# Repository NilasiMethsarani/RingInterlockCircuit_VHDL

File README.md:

Ring Interlock Circuit for EV Charging

This repository contains the design and implementation of a Ring Interlock Circuit for electric vehicle (EV) charging, using a CPLD (Complex Programmable Logic Device), specifically the EPM240T100C5N. The interlock circuit enhances the safety, efficiency, and reliability of EV charging systems by ensuring dynamic power sharing and robust fault prevention mechanisms.
Key Features

    Dynamic Power Sharing: Efficient distribution of power between multiple EVs to optimize charging performance.
    Enhanced Prioritization: Ensures prioritized power delivery based on load requirements.
    Short Circuit Prevention: Detects and prevents potential short circuits during charging.
    Compact and Scalable Design: Designed for scalability, leveraging the EPM240T100C5N CPLD for cost-effective implementation.

Design Components

    Technology Used:
        CPLD Model: EPM240T100C5N
        Quartus Prime for synthesis and implementation.
        ModelSim for simulation.
        Proteus for circuit-level design and testing.

    Input Signals:
        EV charging status.
        Fault detection inputs.
        Load conditions for power prioritization.

    Output Signals:
        Control signals to charging ports.
        Fault notifications.
        Power allocation indicators.

Objectives

    Ensure safe and efficient charging of multiple EVs using an interlock mechanism.
    Provide a cost-effective solution with minimal hardware overhead.
    Test and validate the design against real-world fault conditions.

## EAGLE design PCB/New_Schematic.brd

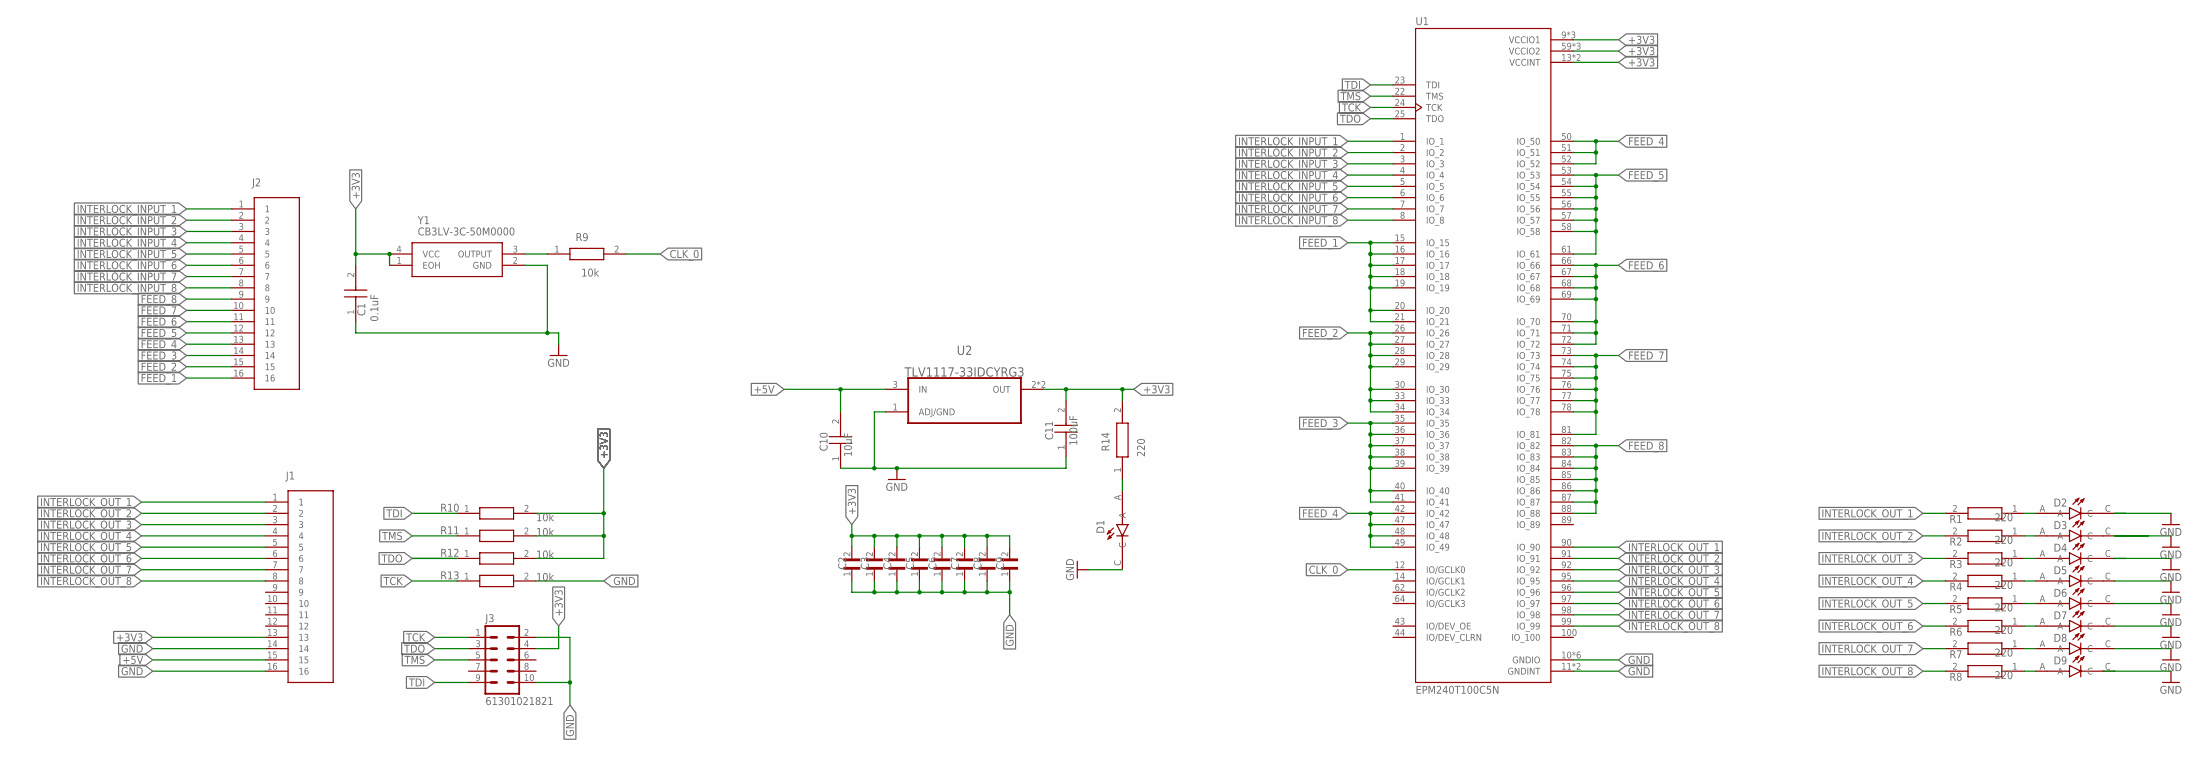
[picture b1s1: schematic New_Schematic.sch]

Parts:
C1: GRM188R71C104MA01D; CAPC1608X90N
C2, C3, C4, C5, C6, C7, C8, C9: GRM155R70J104KA01D; CAPC1005X55N
C10, C11: 0603X106M160CT; CAPC1608X95N
D1, D2, D3, D4, D5, D6, D7, D8, D9: HSMS-C190; LEDM1608X80
J1, J2: 1-2314812-6; TE_1-2314812-6
J3: 61301021821; 2X05-PIN
R1, R2, R3, R4, R5, R6, R7, R8, R14: MCT06030D2200BP100; RESC1608X55N
R9, R10, R11, R12, R13: CRT0603-BY-1002EAS; RESC1608X60N
U1: EPM240T100C5N; QFP50P1600X1600X120-100N
U2: TLV1117-33IDCYRG3; SOT230P700X180-4N
Y1: CB3LV-3C-50M0000; CB3LV3C50M0000

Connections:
+3V3: C1.2, C2.2, C3.2, C4.2, C5.2, C6.2, C7.2, C8.2, C9.2, C11.2, J1.13, J3.4, R10.2, R11.2, R12.2, R14.2, U1.9 (VCCIO1), U1.13 (VCCINT), U1.31 (VCCIO1), U1.45 (VCCIO1), U1.59 (VCCIO2), U1.63 (VCCINT), U1.80 (VCCIO2), U1.94 (VCCIO2), U2.2 (OUT), U2.4 (OUT), Y1.1 (EOH), Y1.4 (VCC)
+5V: C10.2, J1.15, U2.3 (IN)
CLK_0: R9.2, U1.12 (IO/GCLK0)
FEED_1: J2.16, U1.15 (IO_15), U1.16 (IO_16), U1.17 (IO_17), U1.18 (IO_18), U1.19 (IO_19), U1.20 (IO_20), U1.21 (IO_21)
FEED_2: J2.15, U1.26 (IO_26), U1.27 (IO_27), U1.28 (IO_28), U1.29 (IO_29), U1.30 (IO_30), U1.33 (IO_33), U1.34 (IO_34)
FEED_3: J2.14, U1.35 (IO_35), U1.36 (IO_36), U1.37 (IO_37), U1.38 (IO_38), U1.39 (IO_39), U1.40 (IO_40), U1.41 (IO_41)
FEED_4: J2.13, U1.42 (IO_42), U1.47 (IO_47), U1.48 (IO_48), U1.49 (IO_49), U1.50 (IO_50), U1.51 (IO_51), U1.52 (IO_52)
FEED_5: J2.12, U1.53 (IO_53), U1.54 (IO_54), U1.55 (IO_55), U1.56 (IO_56), U1.57 (IO_57), U1.58 (IO_58), U1.61 (IO_61)
FEED_6: J2.11, U1.66 (IO_66), U1.67 (IO_67), U1.68 (IO_68), U1.69 (IO_69), U1.70 (IO_70), U1.71 (IO_71), U1.72 (IO_72)
FEED_7: J2.10, U1.73 (IO_73), U1.74 (IO_74), U1.75 (IO_75), U1.76 (IO_76), U1.77 (IO_77), U1.78 (IO_78), U1.81 (IO_81)
FEED_8: J2.9, U1.82 (IO_82), U1.83 (IO_83), U1.84 (IO_84), U1.85 (IO_85), U1.86 (IO_86), U1.87 (IO_87), U1.88 (IO_88)
GND: C1.1, C2.1, C3.1, C4.1, C5.1, C6.1, C7.1, C8.1, C9.1, C10.1, C11.1, D1.C, D2.C, D3.C, D4.C, D5.C, D6.C, D7.C, D8.C, D9.C, J1.14, J1.16, J3.2, J3.10, R13.2, U1.10 (GNDIO), U1.11 (GNDINT), U1.32 (GNDIO), U1.46 (GNDIO), U1.60 (GNDIO), U1.65 (GNDINT), U1.79 (GNDIO), U1.93 (GNDIO), U2.1 (ADJ/GND), Y1.2 (GND)
INTERLOCK_INPUT_1: J2.1, U1.1 (IO_1)
INTERLOCK_INPUT_2: J2.2, U1.2 (IO_2)
INTERLOCK_INPUT_3: J2.3, U1.3 (IO_3)
INTERLOCK_INPUT_4: J2.4, U1.4 (IO_4)
INTERLOCK_INPUT_5: J2.5, U1.5 (IO_5)
INTERLOCK_INPUT_6: J2.6, U1.6 (IO_6)
INTERLOCK_INPUT_7: J2.7, U1.7 (IO_7)
INTERLOCK_INPUT_8: J2.8, U1.8 (IO_8)
INTERLOCK_OUT_1: J1.1, R1.2, U1.90 (IO_90)
INTERLOCK_OUT_2: J1.2, R2.2, U1.91 (IO_91)
INTERLOCK_OUT_3: J1.3, R3.2, U1.92 (IO_92)
INTERLOCK_OUT_4: J1.4, R4.2, U1.95 (IO_95)
INTERLOCK_OUT_5: J1.5, R5.2, U1.96 (IO_96)
INTERLOCK_OUT_6: J1.6, R6.2, U1.97 (IO_97)
INTERLOCK_OUT_7: J1.7, R7.2, U1.98 (IO_98)
INTERLOCK_OUT_8: J1.8, R8.2, U1.99 (IO_99)
unnamed: D2.A, R1.1
unnamed: D3.A, R2.1
unnamed: D4.A, R3.1
unnamed: D5.A, R4.1
unnamed: D6.A, R5.1
unnamed: D7.A, R6.1
unnamed: D8.A, R7.1
unnamed: D9.A, R8.1
unnamed: R9.1, Y1.3 (OUTPUT)
unnamed: D1.A, R14.1
TCK: J3.1, R13.1, U1.24 (TCK)
TDI: J3.9, R10.1, U1.23 (TDI)
TDO: J3.3, R12.1, U1.25 (TDO)
TMS: J3.5, R11.1, U1.22 (TMS)

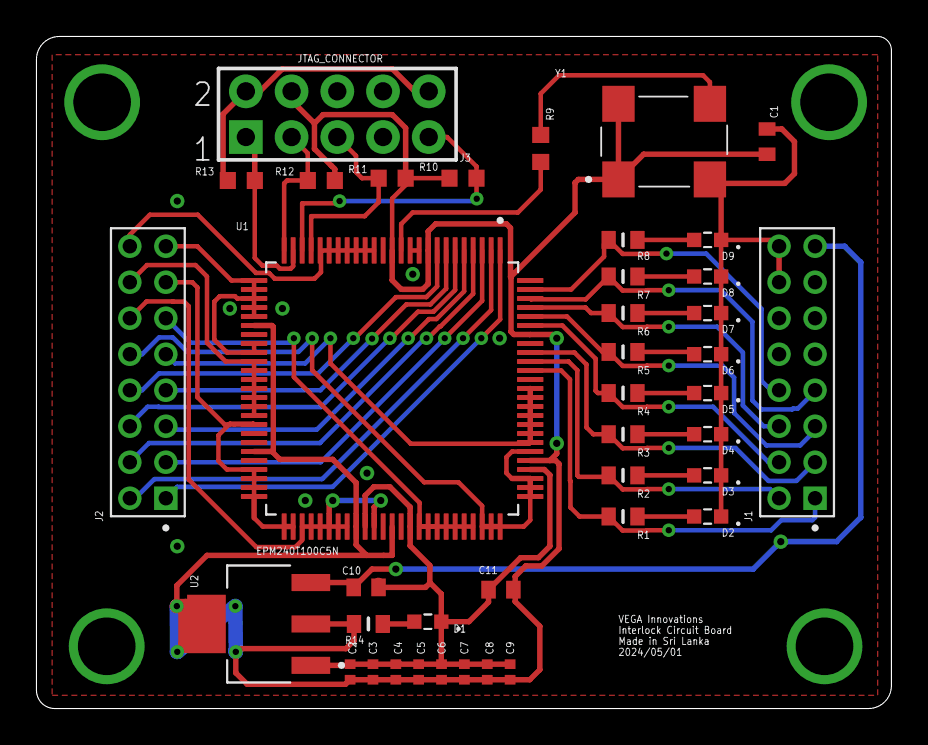
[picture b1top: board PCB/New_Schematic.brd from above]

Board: 2 copper layers, 47.5 x 37.3 mm, 40 parts (0 on the bottom side), 42 nets.

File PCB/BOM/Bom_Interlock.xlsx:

Part | Qty | Manufacturer | Manufacturer Part Number | DigiKey Part Number | LCSC Part Number | Description | Link
J1, J2 | 2 | TE Connectivity AMP Connectors | 1-2314812-6 | 17-1-2314812-6-ND |  | 16P,2MM,B-B,REC,DRVT,2.0,0.1AU,T | Link
J3 | 1 | Würth Elektronik | 61301021821 | 732-2861-ND |  | CONN HDR 10POS 0.1 GOLD PCB | Link
R1, R2, R3, R4, R5, R6, R7, R8, R14 | 9 | Stackpole Electronics Inc | RMCF0603JT220R | RMCF0603JT220RTR-ND |  | RES 220 OHM 5% 1/10W 0603 | Link
R9, R10, R11, R12, R13 | 5 | Bourns Inc. | CRT0603-BY-1002EAS | CRT0603-BY-1002EASTR-ND |  | RES SMD 10K OHM 1/10W 0.1% 0603 | Link
C1, C2, C3, C4, C5, C6, C7, C8, C9 | 9 | Murata Electronics | GRM188R71C104MA01D | 490-11510-2-ND |  | CAP CER 0.1UF 16V X7R 0603 | Link
C10 | 1 | Murata Electronics | GRM188R61C106MAALD | 490-10729-2-ND |  | CAP CER 10UF 16V X5R 0603 | Link
C11 | 1 | KEMET | C0603C104K4RAC3077 | 399-C0603C104K4RAC3077TR-ND |  | .100UF 16.0V | Link
D1, D2, D3, D4, D5, D6, D7, D8, D9 | 9 | Broadcom Limited | HSMS-C190 | 516-1422-2-ND |  | LED RED DIFFUSED SMD | Link
Y1 | 1 | CTS-Frequency Controls | CB3LV-3C-50M000000 | 110-CB3LV-3C-50M000000TR-ND |  | XTAL OSC XO 50.0000MHZ HCMOS TTL | Link
U1 | 1 | Intel | EPM240T100C5N | 544-1964-ND | C10041 | IC CPLD 192MC 4.7NS 100TQFP | Link
U2 | 1 | Texas Instruments | TLV1117-33IDCYRG3 | 296-50543-2-ND |  | IC REG LIN 3.3V 800MA SOT223-4 | Link

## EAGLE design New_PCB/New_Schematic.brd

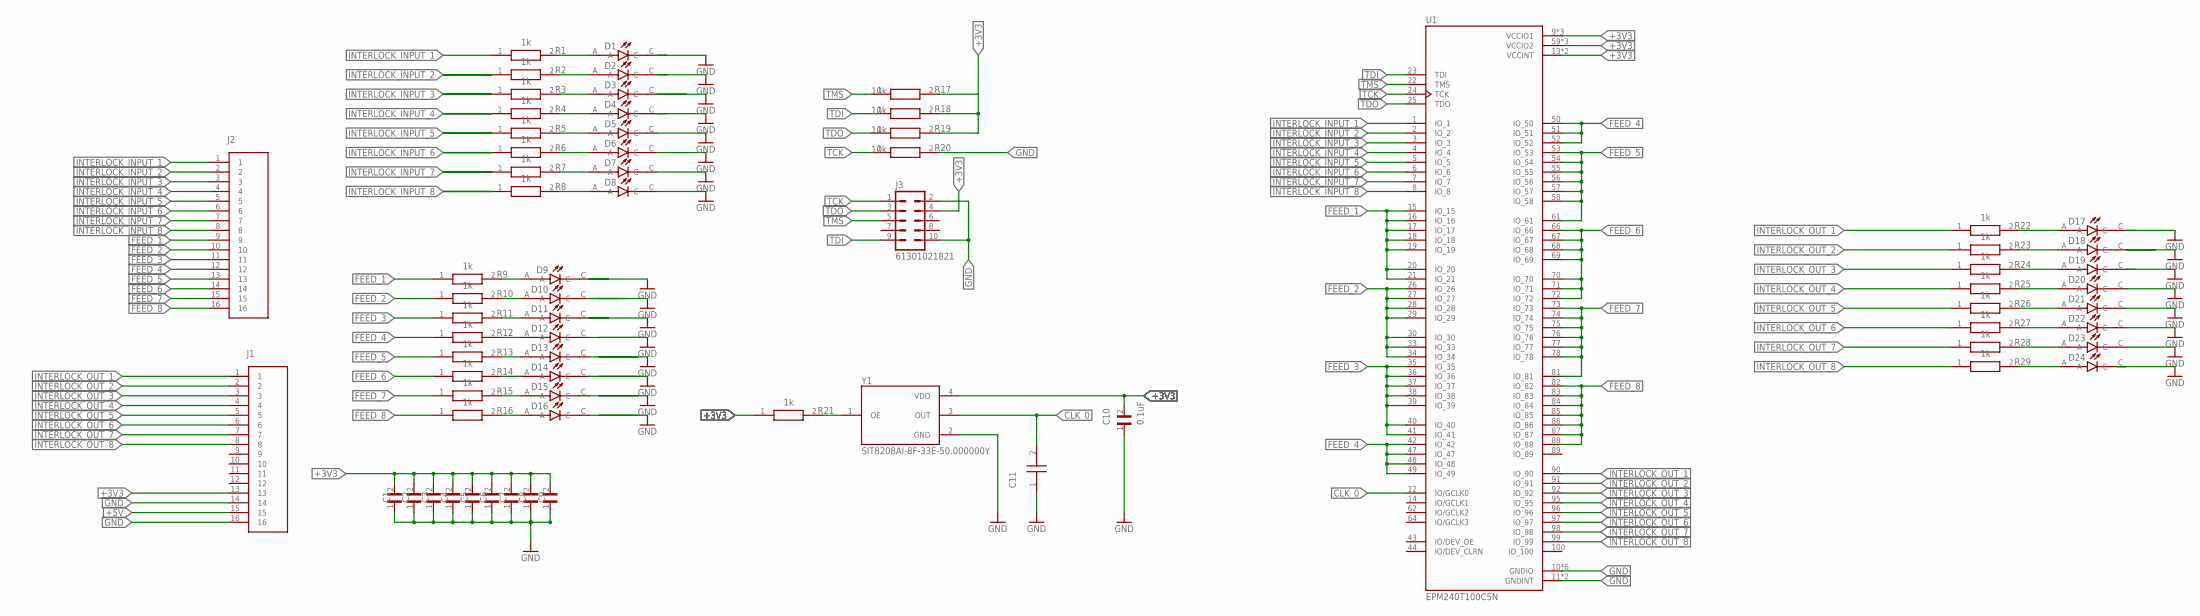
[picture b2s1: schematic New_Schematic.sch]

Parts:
C1, C2, C3, C4, C5, C6, C7, C8, C9, C10: GRM155R70J104KA01D; CAPC1005X55N
C11: GRM1883U2A150JZ01B; CAPC1608X90N
D1, D2, D3, D4, D5, D6, D7, D8, D9, D10, D11, D12, D13, D14, D15, D16, D17, D18, D19, D20, D21, D22, D23, D24: HSMS-C190; LEDM1608X80
J1, J2: 1-2314812-6; TE_1-2314812-6
J3: 61301021821; 2X05-PIN
R1, R2, R3, R4, R5, R6, R7, R8, R9, R10, R11, R12, R13, R14, R15, R16, R21, R22, R23, R24, R25, R26, R27, R28, R29: ERJS03D1001V; RESC1608X55N
R17, R18, R19, R20: CRT0603-BY-1002EAS; RESC1608X60N
U1: EPM240T100C5N; QFP50P1600X1600X120-100N
Y1: SIT8208AI-8F-33E-50.000000Y; OSC_SIT8208AI-8F-33E-50.000000Y

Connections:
+3V3: C1.2, C2.2, C3.2, C4.2, C5.2, C6.2, C7.2, C8.2, C9.2, C10.2, J1.13, J3.4, R17.2, R18.2, R19.2, R21.1, U1.9 (VCCIO1), U1.13 (VCCINT), U1.31 (VCCIO1), U1.45 (VCCIO1), U1.59 (VCCIO2), U1.63 (VCCINT), U1.80 (VCCIO2), U1.94 (VCCIO2), Y1.4 (VDD)
+5V: J1.15
CLK_0: C11.2, U1.12 (IO/GCLK0), Y1.3 (OUT)
FEED_1: J2.9, R9.1, U1.15 (IO_15), U1.16 (IO_16), U1.17 (IO_17), U1.18 (IO_18), U1.19 (IO_19), U1.20 (IO_20), U1.21 (IO_21)
FEED_2: J2.10, R10.1, U1.26 (IO_26), U1.27 (IO_27), U1.28 (IO_28), U1.29 (IO_29), U1.30 (IO_30), U1.33 (IO_33), U1.34 (IO_34)
FEED_3: J2.11, R11.1, U1.35 (IO_35), U1.36 (IO_36), U1.37 (IO_37), U1.38 (IO_38), U1.39 (IO_39), U1.40 (IO_40), U1.41 (IO_41)
FEED_4: J2.12, R12.1, U1.42 (IO_42), U1.47 (IO_47), U1.48 (IO_48), U1.49 (IO_49), U1.50 (IO_50), U1.51 (IO_51), U1.52 (IO_52)
FEED_5: J2.13, R13.1, U1.53 (IO_53), U1.54 (IO_54), U1.55 (IO_55), U1.56 (IO_56), U1.57 (IO_57), U1.58 (IO_58), U1.61 (IO_61)
FEED_6: J2.14, R14.1, U1.66 (IO_66), U1.67 (IO_67), U1.68 (IO_68), U1.69 (IO_69), U1.70 (IO_70), U1.71 (IO_71), U1.72 (IO_72)
FEED_7: J2.15, R15.1, U1.73 (IO_73), U1.74 (IO_74), U1.75 (IO_75), U1.76 (IO_76), U1.77 (IO_77), U1.78 (IO_78), U1.81 (IO_81)
FEED_8: J2.16, R16.1, U1.82 (IO_82), U1.83 (IO_83), U1.84 (IO_84), U1.85 (IO_85), U1.86 (IO_86), U1.87 (IO_87), U1.88 (IO_88)
GND: C1.1, C2.1, C3.1, C4.1, C5.1, C6.1, C7.1, C8.1, C9.1, C10.1, C11.1, D1.C, D2.C, D3.C, D4.C, D5.C, D6.C, D7.C, D8.C, D9.C, D10.C, D11.C, D12.C, D13.C, D14.C, D15.C, D16.C, D17.C, D18.C, D19.C, D20.C, D21.C, D22.C, D23.C, D24.C, J1.14, J1.16, J3.2, J3.10, R20.2, U1.10 (GNDIO), U1.11 (GNDINT), U1.32 (GNDIO), U1.46 (GNDIO), U1.60 (GNDIO), U1.65 (GNDINT), U1.79 (GNDIO), U1.93 (GNDIO), Y1.2 (GND)
INTERLOCK_INPUT_1: J2.1, R1.1, U1.1 (IO_1)
INTERLOCK_INPUT_2: J2.2, R2.1, U1.2 (IO_2)
INTERLOCK_INPUT_3: J2.3, R3.1, U1.3 (IO_3)
INTERLOCK_INPUT_4: J2.4, R4.1, U1.4 (IO_4)
INTERLOCK_INPUT_5: J2.5, R5.1, U1.5 (IO_5)
INTERLOCK_INPUT_6: J2.6, R6.1, U1.6 (IO_6)
INTERLOCK_INPUT_7: J2.7, R7.1, U1.7 (IO_7)
INTERLOCK_INPUT_8: J2.8, R8.1, U1.8 (IO_8)
INTERLOCK_OUT_1: J1.1, R22.1, U1.90 (IO_90)
INTERLOCK_OUT_2: J1.2, R23.1, U1.91 (IO_91)
INTERLOCK_OUT_3: J1.3, R24.1, U1.92 (IO_92)
INTERLOCK_OUT_4: J1.4, R25.1, U1.95 (IO_95)
INTERLOCK_OUT_5: J1.5, R26.1, U1.96 (IO_96)
INTERLOCK_OUT_6: J1.6, R27.1, U1.97 (IO_97)
INTERLOCK_OUT_7: J1.7, R28.1, U1.98 (IO_98)
INTERLOCK_OUT_8: J1.8, R29.1, U1.99 (IO_99)
unnamed: D2.A, R2.2
unnamed: D3.A, R3.2
unnamed: D4.A, R4.2
unnamed: D5.A, R5.2
unnamed: D6.A, R6.2
unnamed: D7.A, R7.2
unnamed: D8.A, R8.2
unnamed: D16.A, R16.2
unnamed: D1.A, R1.2
unnamed: R21.2, Y1.1 (OE)
unnamed: D9.A, R9.2
unnamed: D17.A, R22.2
unnamed: D18.A, R23.2
unnamed: D10.A, R10.2
unnamed: D11.A, R11.2
unnamed: D12.A, R12.2
unnamed: D13.A, R13.2
unnamed: D14.A, R14.2
unnamed: D15.A, R15.2
unnamed: D19.A, R24.2
unnamed: D20.A, R25.2
unnamed: D21.A, R26.2
unnamed: D22.A, R27.2
unnamed: D23.A, R28.2
unnamed: D24.A, R29.2
TCK: J3.1, R20.1, U1.24 (TCK)
TDI: J3.9, R18.1, U1.23 (TDI)
TDO: J3.3, R19.1, U1.25 (TDO)
TMS: J3.5, R17.1, U1.22 (TMS)

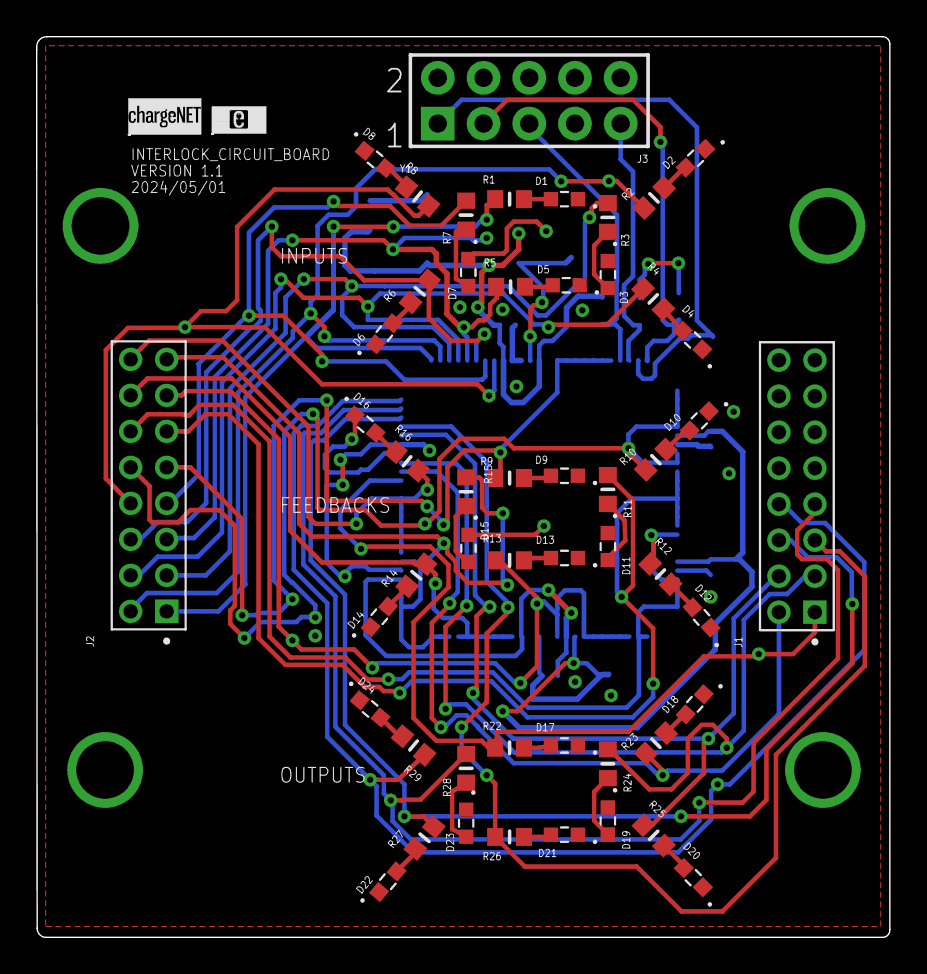
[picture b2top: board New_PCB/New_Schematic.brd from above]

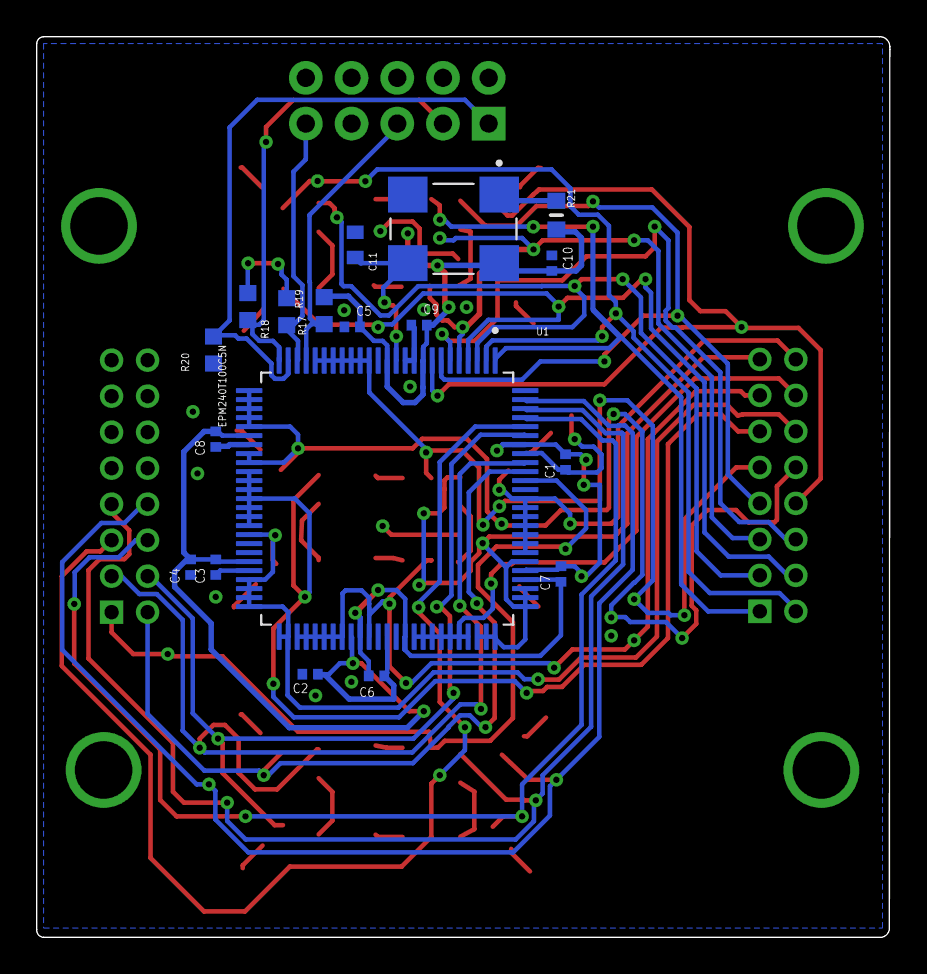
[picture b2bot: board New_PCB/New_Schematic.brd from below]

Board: 4 copper layers, 47.4 x 50.0 mm, 69 parts (18 on the bottom side), 56 nets.
